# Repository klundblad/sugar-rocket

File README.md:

# sugar-rocket
(not a bomb)
Project to measure thrust, bore hole geometries, and make stuff blow up

By Katharine Lundblad, Aidan Phelan, and Oliver Wolf

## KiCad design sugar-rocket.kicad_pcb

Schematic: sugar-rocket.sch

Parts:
D1: D_Schottky; D_SOD-128
D2, D3, D5: LED; LED_D5.0mm
D4, D6: DIODE; D_DO-35_SOD27_P5.08mm_Vertical_KathodeUp
J1: Conn_01x02; Banana_Jack_2Pin
J2: Conn_01x03; Banana_Jack_3Pin
K1: ADW11; Relay_1P1T_NO_10x24x18.8mm_Panasonic_ADW11xxxxW_THT
Q1: BS170; TO-92_Inline
R1, R2, R3: 1k; R_0805_2012Metric_Pad1.20x1.40mm_HandSolder
R4, R5: 10k; R_0805_2012Metric_Pad1.20x1.40mm_HandSolder
SW1: SW_DPDT_x2; SW_DPDT_CK_JS202011JCQN
SW2: SW_Push; SW_Push_1P1T_NO_6x6mm_H9.5mm

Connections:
+VDC: J2.2, SW1.5 (B)
GND: D3.1 (K), D6.1 (K), J1.1, J2.1, K1.5, K1.6, Q1.3 (S), R1.2, R4.2
unnamed: D1.1 (K), J1.2
unnamed: D1.2 (A), D2.2 (A)
unnamed: D2.1 (K), R1.1
unnamed: D3.2 (A), R2.2
unnamed: D4.1 (K), SW1.2 (B)
unnamed: D4.2 (A), R3.2, SW1.4 (A)
unnamed: D5.1 (K), Q1.1 (D)
unnamed: D5.2 (A), R3.1, R5.1, SW2.2
unnamed: D6.2 (A), K1.1, SW1.3 (C)
unnamed: J2.3, K1.3, SW2.1
unnamed: Q1.2 (G), R4.1, R5.2
unnamed: R2.1, SW1.6 (C)

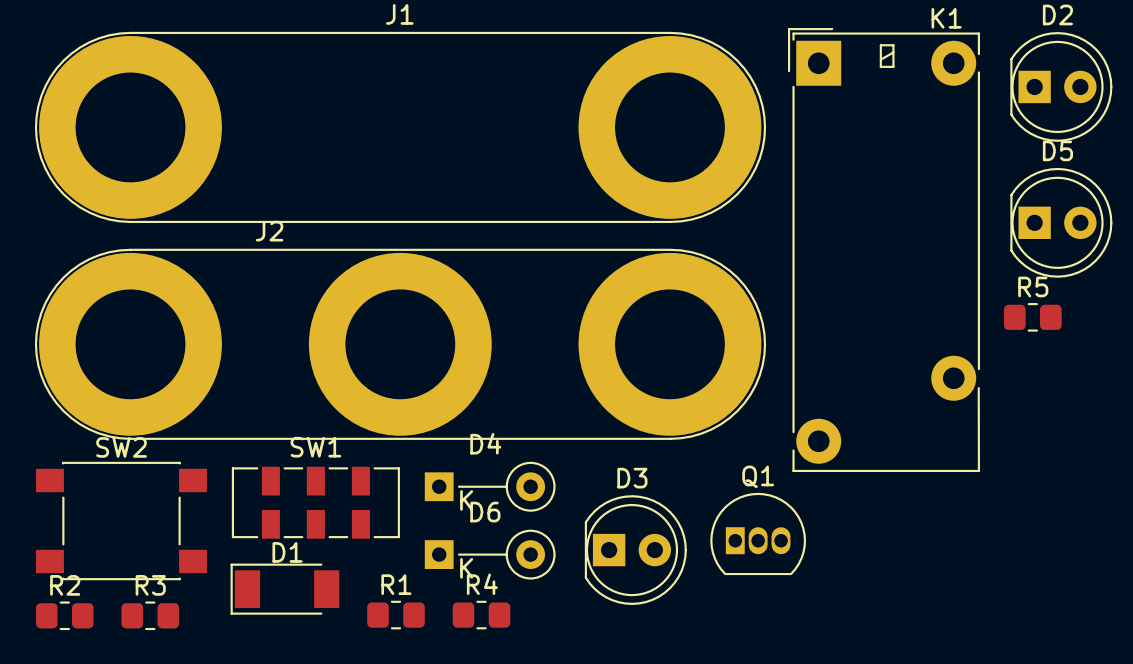
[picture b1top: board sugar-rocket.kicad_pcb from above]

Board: 2 copper layers, 17 parts (0 on the bottom side), 14 nets, no tracks yet.

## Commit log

2021-02-06 Made rocket igniter sch
2021-02-06 made footprints
2021-02-08 Added Aidans partssss
2021-02-09 Power supply for a 9-35V Battery
2021-02-11 Power supply, ATTiny, and igniter relay git add L7805.step!
2021-02-11 Rename L7805.lib to igniter-controller/transistor-pretty/L7805.lib
2021-02-11 Rename L7805.step to igniter-controller/transistor-pretty/L7805.step
